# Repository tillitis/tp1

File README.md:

# TKey Programmer 1

The TKey Programmer 1 (TP1) board is a tool used to program the FPGA
on a TKey. It consists of a RPI Pico and a jig where the TKey can be
placed.

## General usage

The board is interfaced using USB, and it will display itself as ID
`1209:8886 Generic TP-1`. The TKey is supposed to be placed in the jig
and one closes the lid carefully by pressing in the middle of the jig
(by the hole). To open the lid of the jig, it is easiest to simply
lift up on the lever.

The TP1 board supports two host computer tools to accommodate
programming of the TKey, either `iceprog` or `pynvcm`. See the chapter
in the [TKey Developer Handbook](https://dev.tillitis.se/tp1/) for a
more elaborate description on how to use it.

## Linux device permissions

To allow sudo-less programming, you need to be able to access the TKey
Programmer USB device. This is a raw USB device that is probably not
taken care of by your distribution.

You can install an udev rule that will assign the TP1 to the dialout
group. You will also need to add your user to the dialout group.

Create the following udev rule at `/etc/udev/rules.d`:

```
# TP-1 programmer
SUBSYSTEM=="usb", ENV{DEVTYPE}=="usb_device", ATTR{idVendor}=="1209", ATTR{idProduct}=="8886", MODE="0666", GROUP="dialout"
```

To reload the rules run:

```
sudo udevadm control --reload-rules
sudo usermod -aG dialout ${USER}
```

To apply the new group, log out and then log back in, or run the
command `newgrp dialout` in the terminal that you are working in.

You can check the device permissions to determine if the group was
successfully applied. First, use `lsusb` to find the location of the
programmer:

```
lsusb -d 1209:8886
Bus 001 Device 023: ID 1209:8886 Generic TP-1
```

Then, you can check the permissions by using the bus and device
numbers reported above like this:

```
ls -l /dev/bus/usb/001/023
crw-rw---- 1 root dialout 189, 22 Feb 16 14:58 /dev/bus/usb/001/023
```

Note that this pair of numbers is ephemeral and may change after every
device insertion.

## Firmware
The TP1 board runs a custom firmware developed by Blinkinlabs for
Tillitis. There is also a pre-built firmware binary at
`fw/bin/main.uf2`.

To update the firmware, either build the file `main.uf2` (more
instructions below) or get the pre-built file to your host computer.
Then do the following:

1. Disconnect the programming board from the host computer
2. Press and hold the "BOOTSEL" button on the RPi2040 sub-board on the
programming board
3. Reconnect the programming board to the host computer
4. Release the "BOOTSEL" button after connecting the programming board
to the host. The board should now appear to the host as a USB
connected storage device
5. Open the storage device and drop the firmware file `main.uf2` into
the storage device

The programmer will update its firmware with the file and restart
itself. After rebooting, the storage device will automatically be
disconnected.

### Building the firmware

The firmware requires the Raspberry Pi Pico SDK, the build script
assumes this is located either in your home home directory, or in
`/usr/local`. To clone to the home directory use

```
cd ~
git clone --branch 1.5.1 https://github.com/raspberrypi/pico-sdk.git
cd pico-sdk
git submodule update --init
```

then run the build script in the `fw` folder

```
./build.sh
```

Note that our container image (tkey-builder) places the pico-sdk
directory in `/usr/local`. For normal development, it is usually left
in the user's home directory.

See
[fw/README.md](https://github.com/tillitis/tp1/blob/main/fw//README.md)
for further instructions.

## KiCad

The PCB is built using KiCad version 7. Production files are built in
CI using KiBot, see the Makefile for exact version.

## License
### Hardware
Unless otherwise noted, this project is licensed under CERN Open
Hardware License Version 2 - Strongly Reciprocal, see full license
under [LICENSE.txt](/LICENSE.txt).
```
Copyright Tillitis AB 2022-2024.

This source describes Open Hardware and is licensed under the CERN-OHL-S v2.

You may redistribute and modify this source and make products using it under
the terms of the CERN-OHL-S v2 (https://ohwr.org/cern_ohl_s_v2.txt).

This source is distributed WITHOUT ANY EXPRESS OR IMPLIED WARRANTY,
INCLUDING OF MERCHANTABILITY, SATISFACTORY QUALITY AND FITNESS FOR A
PARTICULAR PURPOSE. Please see the CERN-OHL-S v2 for applicable conditions.

Source location: https://github.com/tillitis/tp1

As per CERN-OHL-S v2 section 4, should You produce hardware based on this
source, You must where practicable maintain the Source Location visible
on the external case of the product or its packaging, and in its
documentation, even after modification.
```

The [CERN-OHL-S user guide](/User-guide-CERN-OHL-S.txt) is included to
make it easier to follow the license, both as a Licensor or a Licensee.

### Firmware
The firmware running on the TP1 is licensed under MIT License, see the
full license [fw/LICENSE](fw/LICENSE).

Copyright (c) 2023 Tillitis AB.

### Raspberry Pi Pico
TKey Programmer board uses the Raspberry Pi Pico hardware, which are
provided by Raspberry Pi Ltd. For more details, visit the official
Raspberry Pi Pico documentation at
https://www.raspberrypi.com/licensing/

## Prototypes

Under `prototypes/`, an earlier version of the TP1 can be found, such as
the `mta1-usb-v1-programmer`.

## History
This repo was created by filtering out relevant commits and files from
the [tillitis/tillits-key1](https://github.com/tillitis/tillitis-key1)
repo.

The filtering removed all files and commits that weren't related to
the tp1 hardware. This was done using
[git-filter-repo](https://github.com/newren/git-filter-repo).

To replicate the results up until commit `f1158b1` in this repo,
checkout commit `354aecb` in `tillitis/tillitis-key1` and run
`git-filter-repo --path hw/boards/tp1 --path
hw/boards/mta1-usb-v1-programmer --path hw/boards/KiCad-RP Pico`

All filtered commits have intact date, author, and code. Some
unrelated files are removed from some commits, but the commit messages
are left unchanged. Commit sha, tags and signatures are new. For
complete history, please see tillitis/tillitis-key1 from commit
`354aecb` and earlier.

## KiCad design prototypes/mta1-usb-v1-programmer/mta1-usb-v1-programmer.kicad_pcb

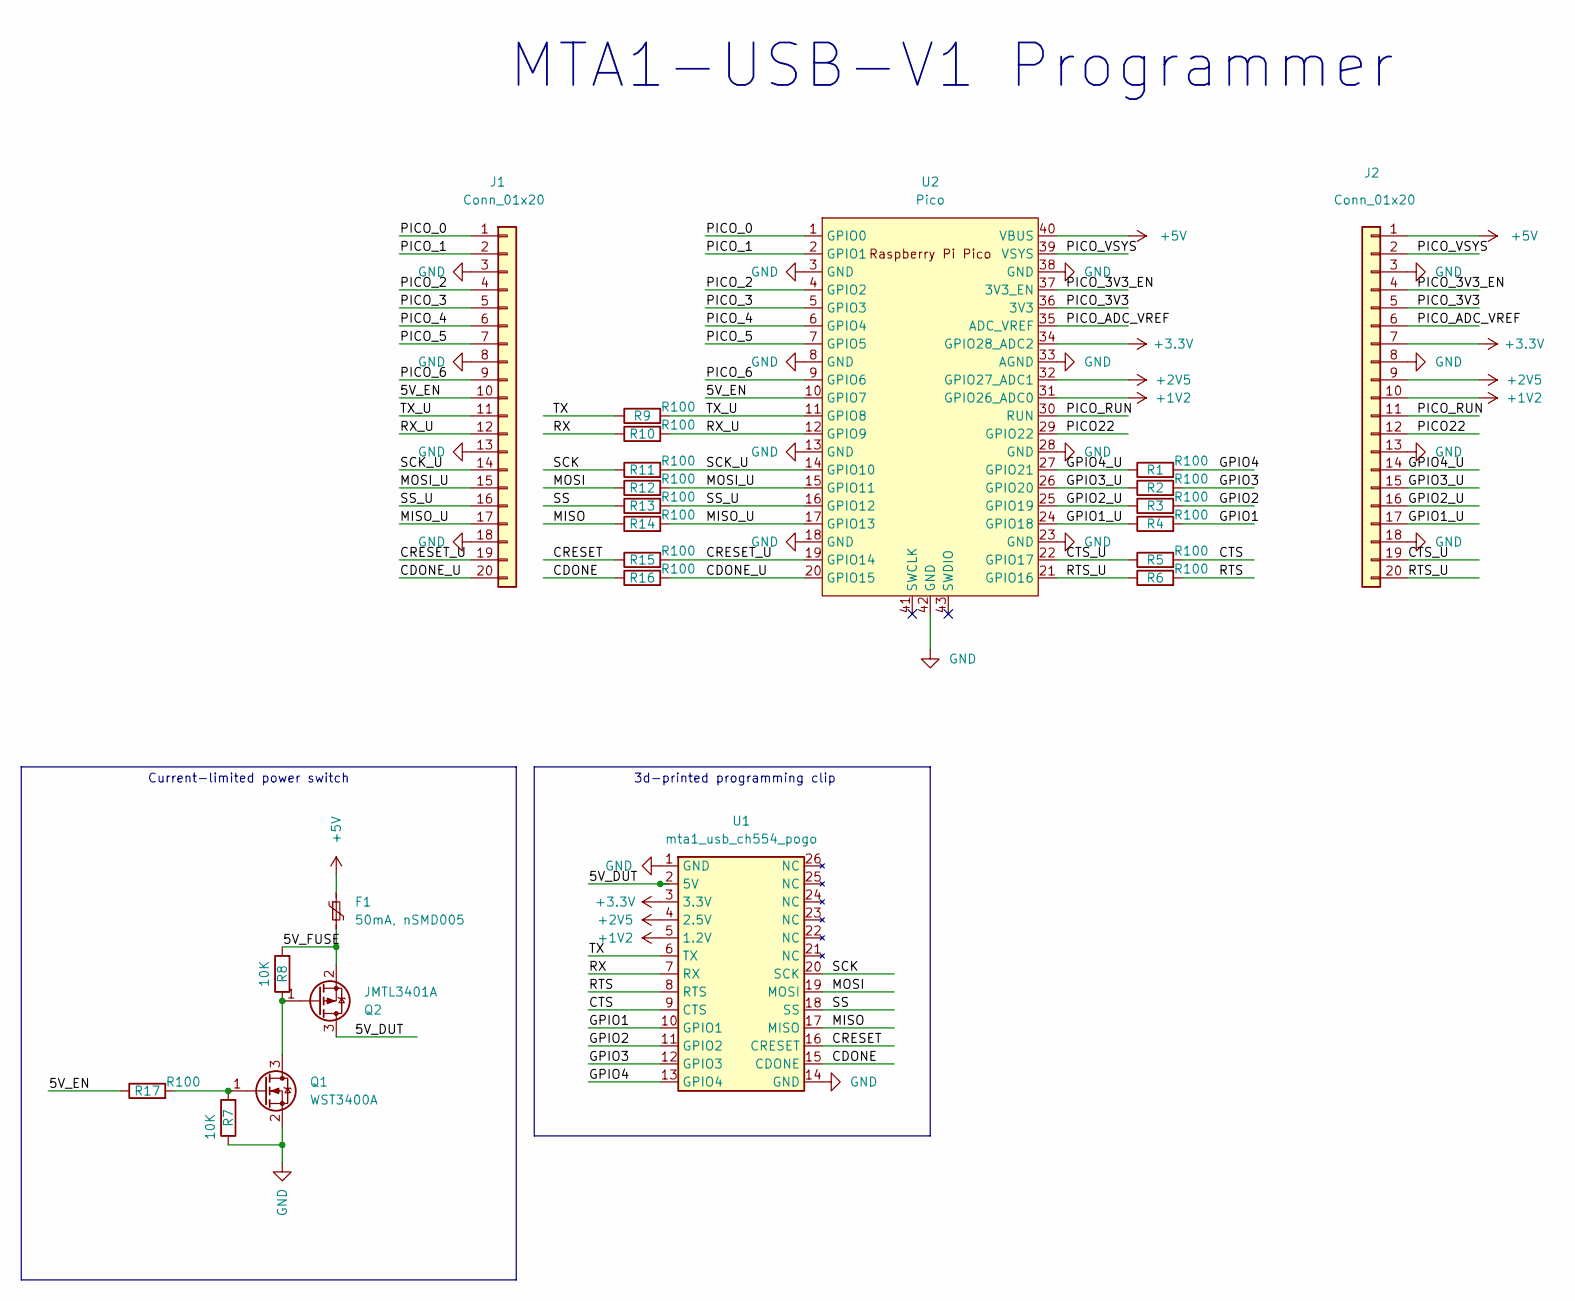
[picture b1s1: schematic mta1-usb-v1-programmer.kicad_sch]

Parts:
F1: 50mA, nSMD005; Fuse_1206_3216Metric; Manufacturer Part Number SMD1206P005TF
J1, J2: Conn_01x20; PinHeader_1x20_P2.54mm_Vertical
Q1: WST3400A; SOT-23; Manufacturer Part Number WST3400A
Q2: JMTL3401A; SOT-23; Manufacturer Part Number JMTL3401A
R1, R2, R3, R4, R5, R6, R9, R10, R11, R12, R13, R14, R15, R16, R17: R100; ERJ2G(0402)_L; Manufacturer Part Number AF0402FR-07100RL
R7, R8: 10K; ERJ2G(0402)_L; Manufacturer Part Number AT0402FRE0710KL
U1: mta1_usb_ch554_pogo
U2: Pico; RPi_Pico_SMD_TH; Manufacturer Part Number SC0915

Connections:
+1V2: J2.10, U1.5 (1.2V), U2.31 (GPIO26_ADC0)
+2V5: J2.9, U1.4 (2.5V), U2.32 (GPIO27_ADC1)
+3V3: J2.7, U1.3 (3.3V), U2.34 (GPIO28_ADC2)
+5V: F1.1, J2.1, U2.40 (VBUS)
/5V_DUT: Q2.3 (D), U1.2 (5V)
/5V_EN: J1.10, R17.1, U2.10 (GPIO7)
/5V_FUSE: F1.2, Q2.2 (S), R8.2
/CDONE: R16.1, U1.15 (CDONE)
/CDONE_U: J1.20, R16.2, U2.20 (GPIO15)
/CRESET: R15.1, U1.16 (CRESET)
/CRESET_U: J1.19, R15.2, U2.19 (GPIO14)
/CTS: R5.2, U1.9 (CTS)
/CTS_U: J2.19, R5.1, U2.22 (GPIO17)
/GPIO1: R4.2, U1.10 (GPIO1)
/GPIO1_U: J2.17, R4.1, U2.24 (GPIO18)
/GPIO2: R3.2, U1.11 (GPIO2)
/GPIO2_U: J2.16, R3.1, U2.25 (GPIO19)
/GPIO3: R2.2, U1.12 (GPIO3)
/GPIO3_U: J2.15, R2.1, U2.26 (GPIO20)
/GPIO4: R1.2, U1.13 (GPIO4)
/GPIO4_U: J2.14, R1.1, U2.27 (GPIO21)
/MISO: R14.1, U1.17 (MISO)
/MISO_U: J1.17, R14.2, U2.17 (GPIO13)
/MOSI: R12.1, U1.19 (MOSI)
/MOSI_U: J1.15, R12.2, U2.15 (GPIO11)
/PICO22: J2.12, U2.29 (GPIO22)
/PICO_0: J1.1, U2.1 (GPIO0)
/PICO_1: J1.2, U2.2 (GPIO1)
/PICO_2: J1.4, U2.4 (GPIO2)
/PICO_3: J1.5, U2.5 (GPIO3)
/PICO_3V3: J2.5, U2.36 (3V3)
/PICO_3V3_EN: J2.4, U2.37 (3V3_EN)
/PICO_4: J1.6, U2.6 (GPIO4)
/PICO_5: J1.7, U2.7 (GPIO5)
/PICO_6: J1.9, U2.9 (GPIO6)
/PICO_ADC_VREF: J2.6, U2.35 (ADC_VREF)
/PICO_RUN: J2.11, U2.30 (RUN)
/PICO_VSYS: J2.2, U2.39 (VSYS)
/RTS: R6.2, U1.8 (RTS)
/RTS_U: J2.20, R6.1, U2.21 (GPIO16)
/RX: R10.1, U1.7 (RX)
/RX_U: J1.12, R10.2, U2.12 (GPIO9)
/SCK: R11.1, U1.20 (SCK)
/SCK_U: J1.14, R11.2, U2.14 (GPIO10)
/SS: R13.1, U1.18 (SS)
/SS_U: J1.16, R13.2, U2.16 (GPIO12)
/TX: R9.1, U1.6 (TX)
/TX_U: J1.11, R9.2, U2.11 (GPIO8)
GND: J1.3, J1.8, J1.13, J1.18, J2.3, J2.8, J2.13, J2.18, Q1.2 (S), R7.1, U1.1 (GND), U1.14 (GND), U2.3 (GND), U2.8 (GND), U2.13 (GND), U2.18 (GND), U2.23 (GND), U2.28 (GND), U2.33 (AGND), U2.38 (GND), U2.42 (GND)
unnamed: Q1.1 (G), R7.2, R17.2
unnamed: Q1.3 (D), Q2.1 (G), R8.1

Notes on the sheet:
Current-limited power switch
MTA1-USB-V1 Programmer
3d-printed programming clip

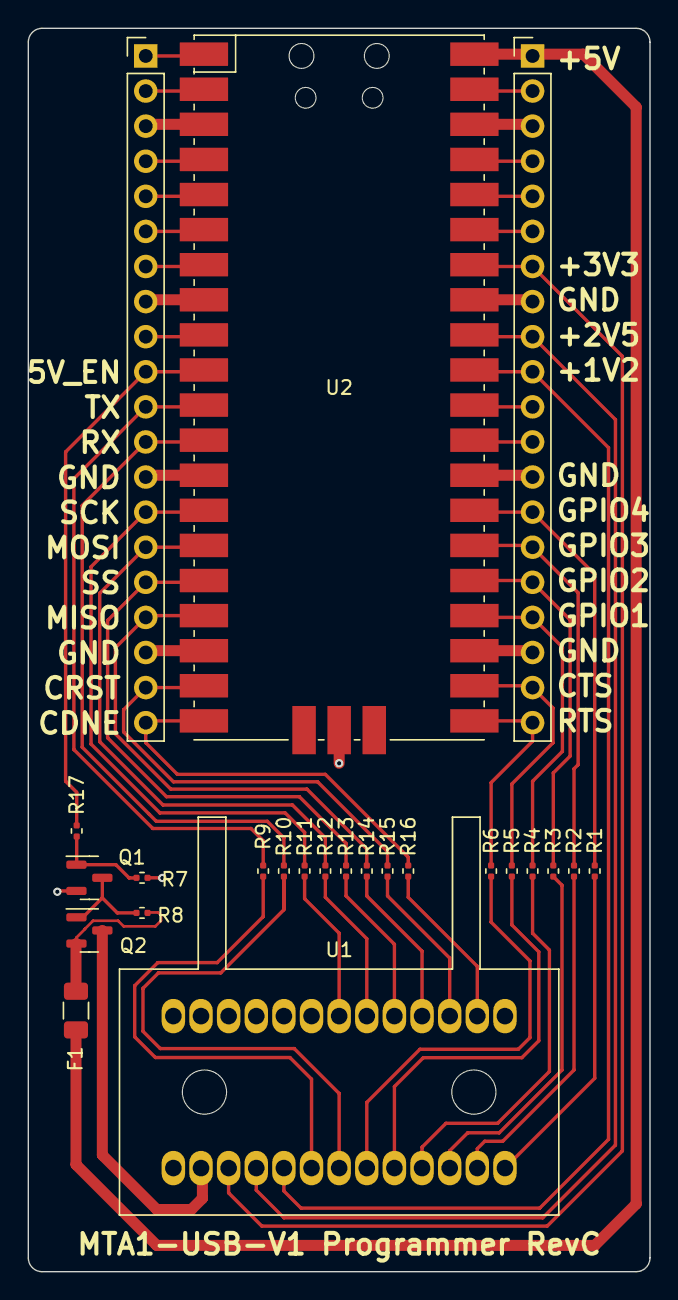
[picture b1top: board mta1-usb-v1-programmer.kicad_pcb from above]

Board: 2 copper layers, 45.0 x 90.0 mm, 24 parts (0 on the bottom side), 51 nets.

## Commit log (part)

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2024-07-05 Make initial public release
2024-07-05 Add modified case plastic design for MTA1 programmer
2024-07-05 Fix broken links in kicad library readme
2024-07-05 TK-1 and TP-1 PCBs (#52)
    * Add kicad library for flat programming clip
    * Add descriptions to part symbols
    * Add extended values, manufacturer/distributor info to components in mta1
    * Add new board entry for TK1
    * Add TP1 programmer design
    * Update MTA1-USB-V1 release files to match production
2024-07-05 Add clip plastic for Acrab release (version 15)
2024-07-05 Add latest (unreleased) clip plastic design
2024-07-05 New plastic clip and update BOM for TP1
2024-07-05 Pull in programmer board firmware
2024-07-05 doc: update to refs to in-tree TP-1 firmware
2024-07-05 pico: change USB vendor to Tillitis
2024-07-05 Add Pico SDK to docker image, for building tp1 firmware
2024-09-05 Move mta1-usb-v1-programmer to prototypes
2024-09-05 Move tp1 directly under hw/
    - Move libraries to `hw/lib/`
    - rename gerbers to gerber
2024-09-05 Moved and filtered commits and files from tillitis/tillitis-key1
    The filtering removes all files and commits that are not related to the
    tp1 hardware. This is done using `git-filter-repo`. To replicate the
    results here, checkout commit `354aecb` in tillitis/tillitis-key1 and
    run `git-filter-repo --path hw/boards/tp1 --path
    hw/boards/mta1-usb-v1-programmer --path hw/boards/KiCad-RP Pico`.
    All commits have intact date, author, and code. Some unrelated files are
2024-09-05 Move firmware to fw/
2024-09-05 CI: add workflow to build firmware
2024-09-05 Fix bug in symbol, pin set to wrong electrical type.
    - Pico: Pin 38 GND set to `Power input` instead of `bidirectional`
2024-09-05 Fix all ERC errors.
    - Update symbols
    - Add PWR_FLAG
2024-09-05 Added mta1-library and updated project links
    - Updated links to symbols, footprints, drawsheet, 3D models
    - Made the links use project defines instead of being absolute
2024-09-05 Fix all DRC errors
    - Update Pico footprint with courtyard and component type
    - Updated 3D model for jig and component type
2024-09-05 Add common gitignore for kicad projects
2024-09-05 Makefile: add targets for firmware
2024-09-05 Update links to library and 3D-models for the prototype mta1-usb-v1-programmer.
2024-09-05 Add Kibot to build in CI
    - Makefile to ease local build
    - Kibot config
    - Filter silkscreen issues
    - Add output to gitignore
2024-09-05 Remove generated files from repository.
    - Keeping generated files makes it harder to keep a consistent version
    control. These files are to be included in the releases.
    - These files can be generated in CI or locally for any commit.
2024-09-20 Add picture of prototype mta1-usb-v1-programmer
2026-06-30 feat(fw): add vendor bulk transfer support
    Implement `tud_vendor_rx_cb()` to handle bulk OUT commands from the host.
    Add support for `COMMAND_SPI_XFER` and `COMMAND_PIN_VALUES`. Handle
    SPI read responses asynchronously via bulk IN in the main loop.
    - Increase `CFG_TUD_VENDOR_RX_BUFSIZE` and `CFG_TUD_VENDOR_TX_BUFSIZE` to 2048
    - Bump `PROTOCOL_VERSION` to 0x0201
